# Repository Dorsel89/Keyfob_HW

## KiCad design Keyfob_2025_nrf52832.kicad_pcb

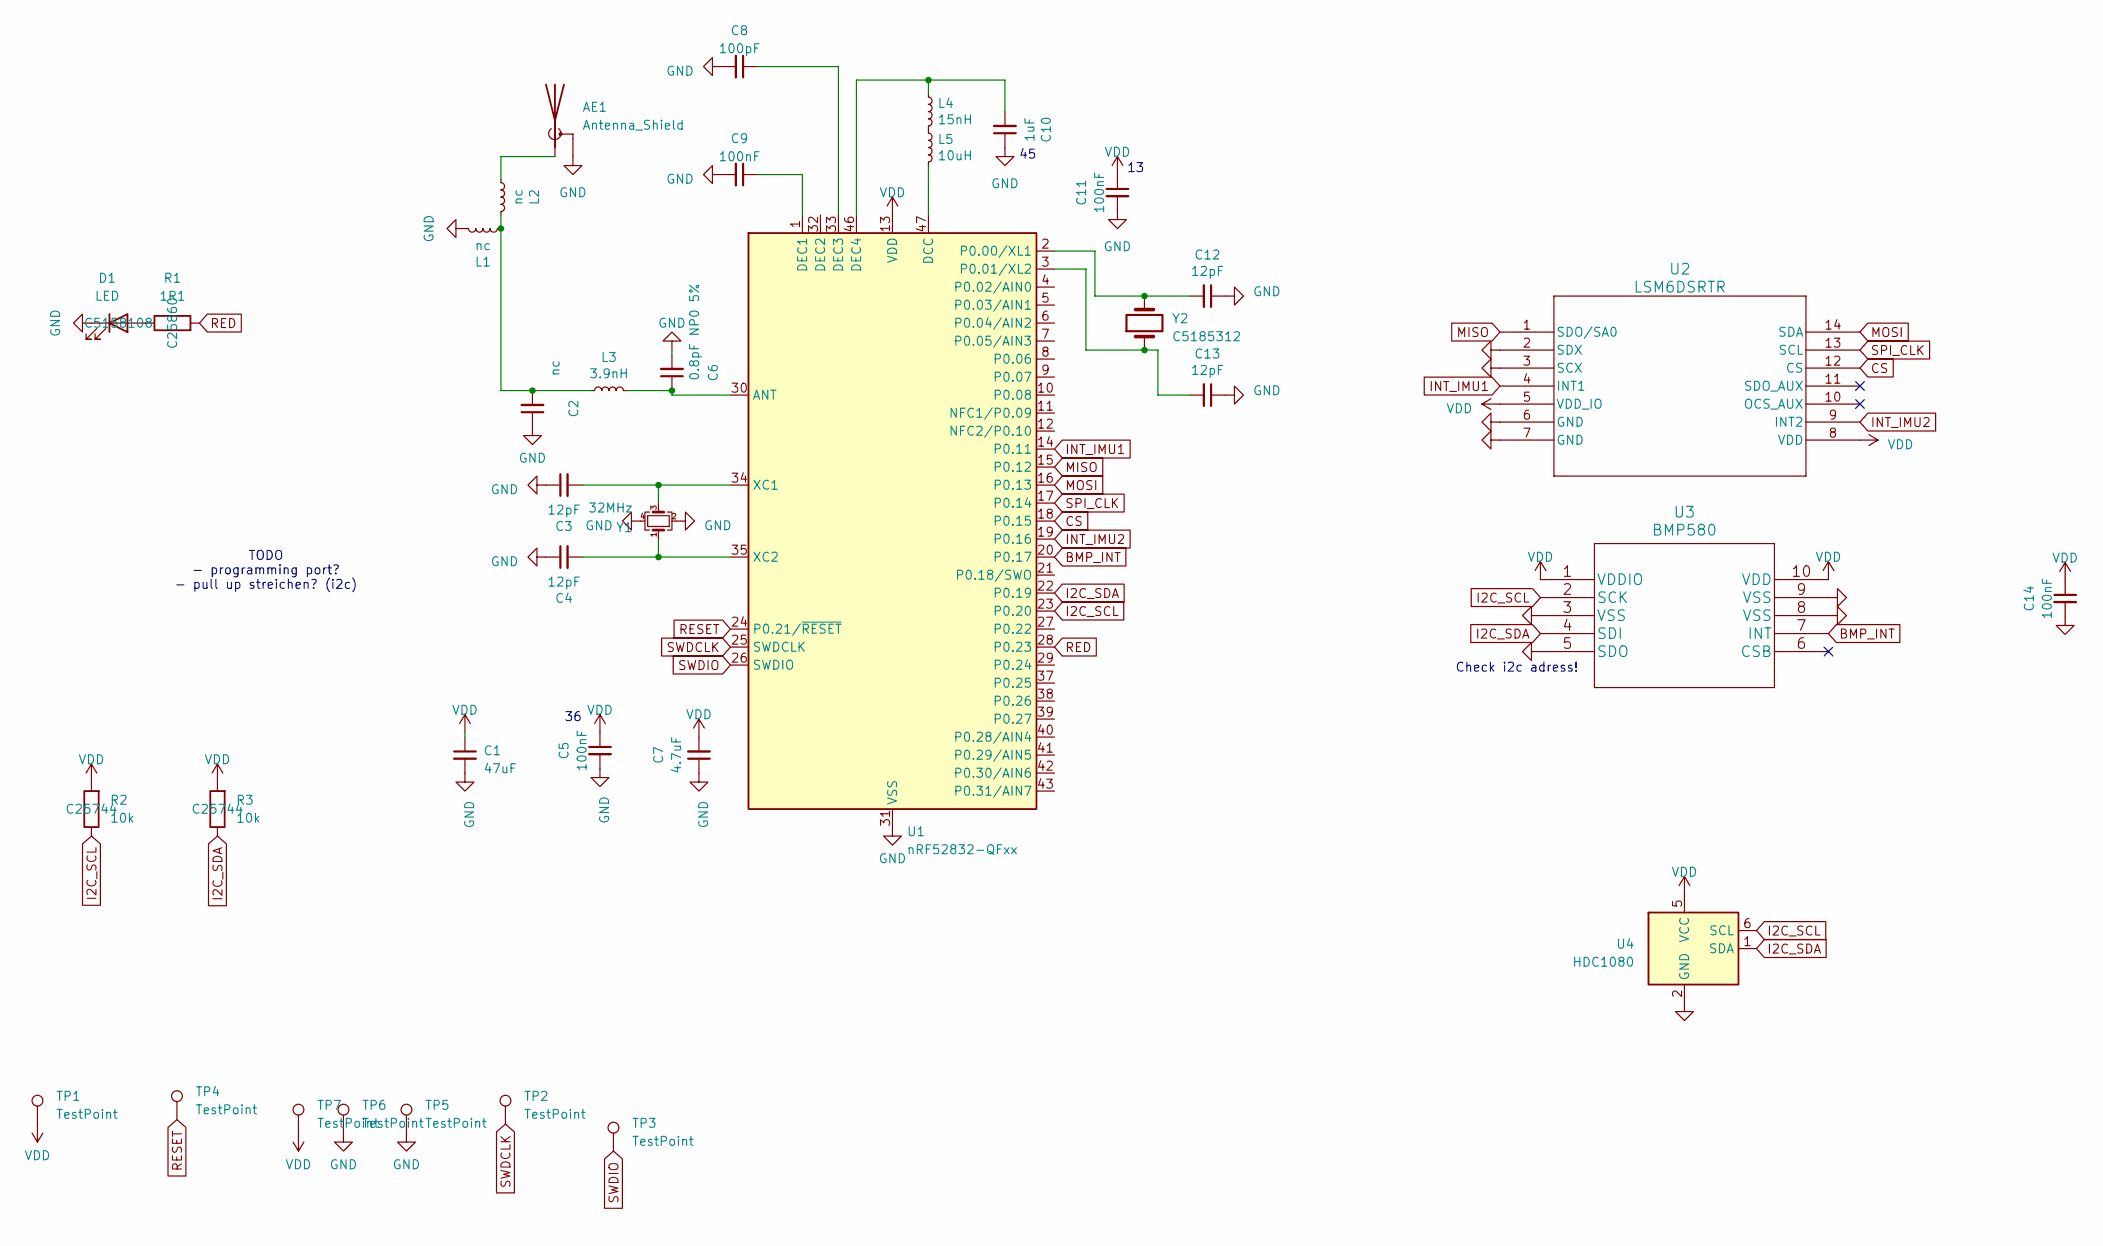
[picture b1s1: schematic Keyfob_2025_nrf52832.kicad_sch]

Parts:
AE1: Antenna_Shield; Texas_SWRA117D_2.4GHz_Right
C1: 47uF; C_0805_2012Metric; Manufacturer Part CL21A476MQYNNNE; LCSC Part C16780
C2: nc; C_0402_1005Metric
C3, C4, C12, C13: 12pF; C_0402_1005Metric; Manufacturer Part CC0402GRNPO9BN120; LCSC Part C526985
C5, C9, C11, C14: 100nF; C_0402_1005Metric; Manufacturer Part CL05B104KA5NNNC; LCSC Part C307331
C6: 0.8pF NP0 5%; C_0402_1005Metric; LCSC Part C76915
C7: 4.7uF; C_0402_1005Metric; Manufacturer Part CL05A475KP5NRNC; LCSC Part C23733
C8: 100pF; C_0402_1005Metric; Manufacturer Part CL05C101JB5NNNC; LCSC Part C1546
C10: 1uF; C_0402_1005Metric; Manufacturer Part CL05A105KO5NNNC; LCSC Part C52923
D1: LED; LED_0402_1005Metric; LCSC C5158108
L1, L2: nc; L_0402_1005Metric
L3: 3.9nH; L_0402_1005Metric; Manufacturer Part MLG1005S3N9BT000; LCSC Part C14033
L4: 15nH; L_0402_1005Metric; Manufacturer Part MLG1005S15NJT000; LCSC Part C27143
L5: 10uH; L_0603_1608Metric; Manufacturer Part MLF1608E100KTD00; LCSC Part C1035
R1: 1R1; R_0402_1005Metric; LCSC C25860
R2, R3: 10k; R_0402_1005Metric; LCSC C25744
TP1: TestPoint; BAT_120TR
TP2, TP3, TP4, TP6, TP7: TestPoint; TestPoint_Pad_D1.0mm
TP5: TestPoint; 112TR
U1: nRF52832-QFxx; QFN-48-1EP_6x6mm_P0.4mm_EP4.6x4.6mm; LCSC Part C77540
U2: LSM6DSRTR; lsm6dsr; LCSC Part C784817
U3: BMP580; BMP581; LCSC Part C22391138
U4: HDC1080; Texas_PWSON-N6; LCSC Part C2864159
Y1: 32MHz; Crystal_SMD_2016-4Pin_2.0x1.6mm; Manufacturer Part X201632MKB4SI; LCSC Part C718072
Y2: C5185312; Crystal_SMD_3215-2Pin_3.2x1.5mm; LCSC Part C5185312

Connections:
BMP_INT: U1.20 (P0.17), U3.7 (INT)
CS: U1.18 (P0.15), U2.12 (CS)
GND: AE1.2 (Shield), C1.2, C2.1, C3.1, C4.1, C5.2, C6.2, C7.1, C8.2, C9.2, C10.1, C11.2, C12.1, C13.1, C14.2, D1.1 (K), L1.2, TP5.1, TP6.1, U1.31 (VSS), U1.45 (VSS), U1.49 (VSS), U2.2 (SDX), U2.3 (SCX), U2.6 (GND), U2.7 (GND), U3.3 (VSS), U3.5 (SDO), U3.8 (VSS), U3.9 (VSS), U4.2 (GND), Y1.2, Y1.4
I2C_SCL: R2.1, U1.23 (P0.20), U3.2 (SCK), U4.6 (SCL)
I2C_SDA: R3.1, U1.22 (P0.19), U3.4 (SDI), U4.1 (SDA)
INT_IMU1: U1.14 (P0.11), U2.4 (INT1)
INT_IMU2: U1.19 (P0.16), U2.9 (INT2)
MISO: U1.15 (P0.12), U2.1 (SDO/SA0)
MOSI: U1.16 (P0.13), U2.14 (SDA)
unnamed: AE1.1 (A), L2.1
unnamed: C2.2, L1.1, L2.2, L3.1
unnamed: D1.2 (A), R1.1
unnamed: L4.2, L5.1
unnamed: C6.1, L3.2, U1.30 (ANT)
unnamed: L5.2, U1.47 (DCC)
unnamed: C9.1, U1.1 (DEC1)
unnamed: C8.1, U1.33 (DEC3)
unnamed: C10.2, L4.1, U1.46 (DEC4)
unnamed: C12.2, U1.2 (P0.00/XL1), Y2.2
unnamed: C13.2, U1.3 (P0.01/XL2), Y2.1
unnamed: C3.2, U1.34 (XC1), Y1.3
unnamed: C4.2, U1.35 (XC2), Y1.1
RED: R1.2, U1.28 (P0.23)
RESET: TP4.1, U1.24 (P0.21/~RESET)
SPI_CLK: U1.17 (P0.14), U2.13 (SCL)
SWDCLK: TP2.1, U1.25 (SWDCLK)
SWDIO: TP3.1, U1.26 (SWDIO)
VDD: C1.1, C5.1, C7.2, C11.1, C14.1, R2.2, R3.2, TP1.1, TP7.1, U1.13 (VDD), U1.36 (VDD), U1.48 (VDD), U2.5 (VDD_IO), U2.8 (VDD), U3.1 (VDDIO), U3.10 (VDD), U4.5 (VCC)

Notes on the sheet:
Check i2c adress!
TODO - programming port? - pull up streichen? (i2c)

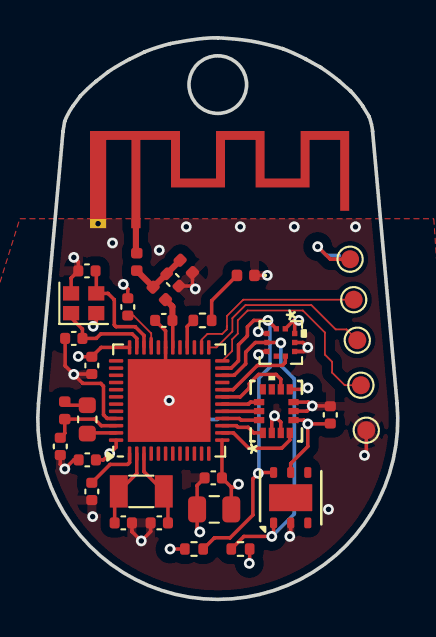
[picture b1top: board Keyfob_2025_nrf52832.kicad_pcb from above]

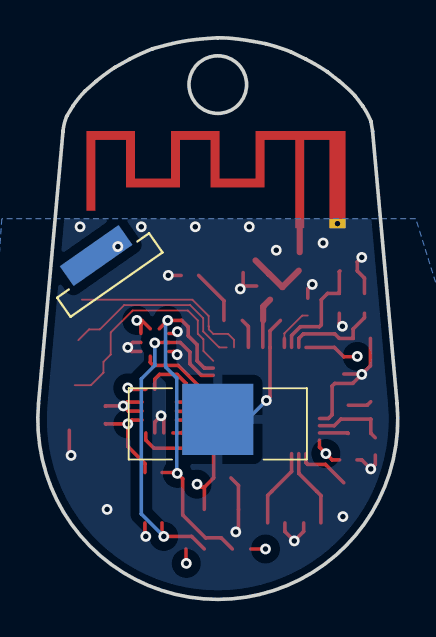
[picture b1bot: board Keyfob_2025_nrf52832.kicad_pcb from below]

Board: 4 copper layers, 20.0 x 31.2 mm, 37 parts (2 on the bottom side), 28 nets.

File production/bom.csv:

Designator,Footprint,Quantity,Value,LCSC Part #
AE1,Texas_SWRA117D_2.4GHz_Right,1,Antenna_Shield,
C1,0805,1,47uF,C16780
C10,0402,1,1uF,C52923
"C11, C14, C5, C9",0402,4,100nF,C307331
"C12, C13, C3, C4",0402,4,12pF,C526985
C6,0402,1,0.8pF NP0 5%,C76915
C7,0402,1,4.7uF,C23733
C8,0402,1,100pF,C1546
D1,0402,1,LED,C5158108
"L1, L2",0402,2,nc,
L3,0402,1,3.9nH,C14033
L4,0402,1,15nH,C27143
L5,0603,1,10uH,C1035
R1,0402,1,1R1,C25860 
"R2, R3",0402,2,10k,C25744 
U1,QFN-48-1EP_6x6mm_P0.4mm_EP4.6x4.6mm,1,nRF52832-QFxx,C77540
U2,lsm6dsr,1,LSM6DSRTR,C784817
U3,BMP581,1,BMP580,C22391138
U4,Texas_PWSON-N6,1,HDC1080,C2864159
Y1,Crystal_SMD_2016-4Pin_2.0x1.6mm,1,32MHz,C718072
Y2,Crystal_SMD_3215-2Pin_3.2x1.5mm,1,C5185312,C5185312
